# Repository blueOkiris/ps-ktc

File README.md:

# Polymath Studio Keyboard/Trackball Combo

NOTE: Project still in development!!!!

## Description

A keyboard and trackball in one, for efficient computer usage.

Like the [PS-OHK](https://github.com/blueOkiris/ps-ohk/), the PS-KTC attempts to provide an efficiently laid out keyboard which doesn't require moving your hands back and forth from the mouse.

Unlike the PS-OHK, it accomplishes this while allowing for typing quickly via using both hands. This is done by placing a trackball in the middle of the keyboard!

## Layout

Like the PS-OHK, the PS-KTC uses a custom keyboard layout designed around placing commonly used characters right on the home row followed by similar sounds being near each other. It also aims to be roughly a 100% keyboard, although a few shortcuts are taken.

Layout:

```
F1  F2  F3  F4  F5  F6                      F7  F8  F9  F10 F11 F12

                Hm  End                     PgU PgD

            3#                                      8*
        2@                                              9(
            F   4%                              7&  L
        D                                               U
Esc 1!      I   K   5%                      6^  P   R       0)
        T                                               O
Tab C       V   A   Y   LClk           RClk H   E   J       M
        X                                               W
Sft S       [{  G   ,<  Scrl                .>  B   ]}      N   `~
        ;:                Whl                          '"
CLk Z       \|  Ins BSp Del               -----     /?      Q
                                         /Track\
    =+  Up      Ctl Sp  Win             | Ball  |           -_   
                                         \     /    
    Lft Dwn Rt  Alt Ret Cmp               -----     
```

Where the home row is S, T, I, A, Space, Trackball, E, R, O, N

There are 82 keys here. Why not 100? Well, there are few reasons:

1. Due to the every key being available and close to a finger in this arrangement, there is no need for the 10 num-pad digits nor the Num Lock nor the num-pad duplicates of /, \*, -, +, Return, and \./Delete. That's 100 - 10 - 7 = 83
2. No Print Screen, Scroll Lock, or Pause because, let's be real, the vast majority of people, myself included, do not need these keys. Maybe Print Screen, but Super + Shift + S is a great key combo for screenshot, so Print Screen is not needed. That's 83 - 3 = 80 keys
3. Mouse clicks as keys. 82 (middle click = left + right)

## Cost

If you go with the recommended JLCPCB, Tindie, and Amazon links, the cost is roughly broken down like so

| Part                    | Cost (w/ shipping) |
|:-----------------------:|:------------------:|
| PCBs                    | $101.01            |
| Motion Sensor           | $39.98             |
| Rotary Encoder  + Wires | $44.20             |
| Total                   | $185.19            |

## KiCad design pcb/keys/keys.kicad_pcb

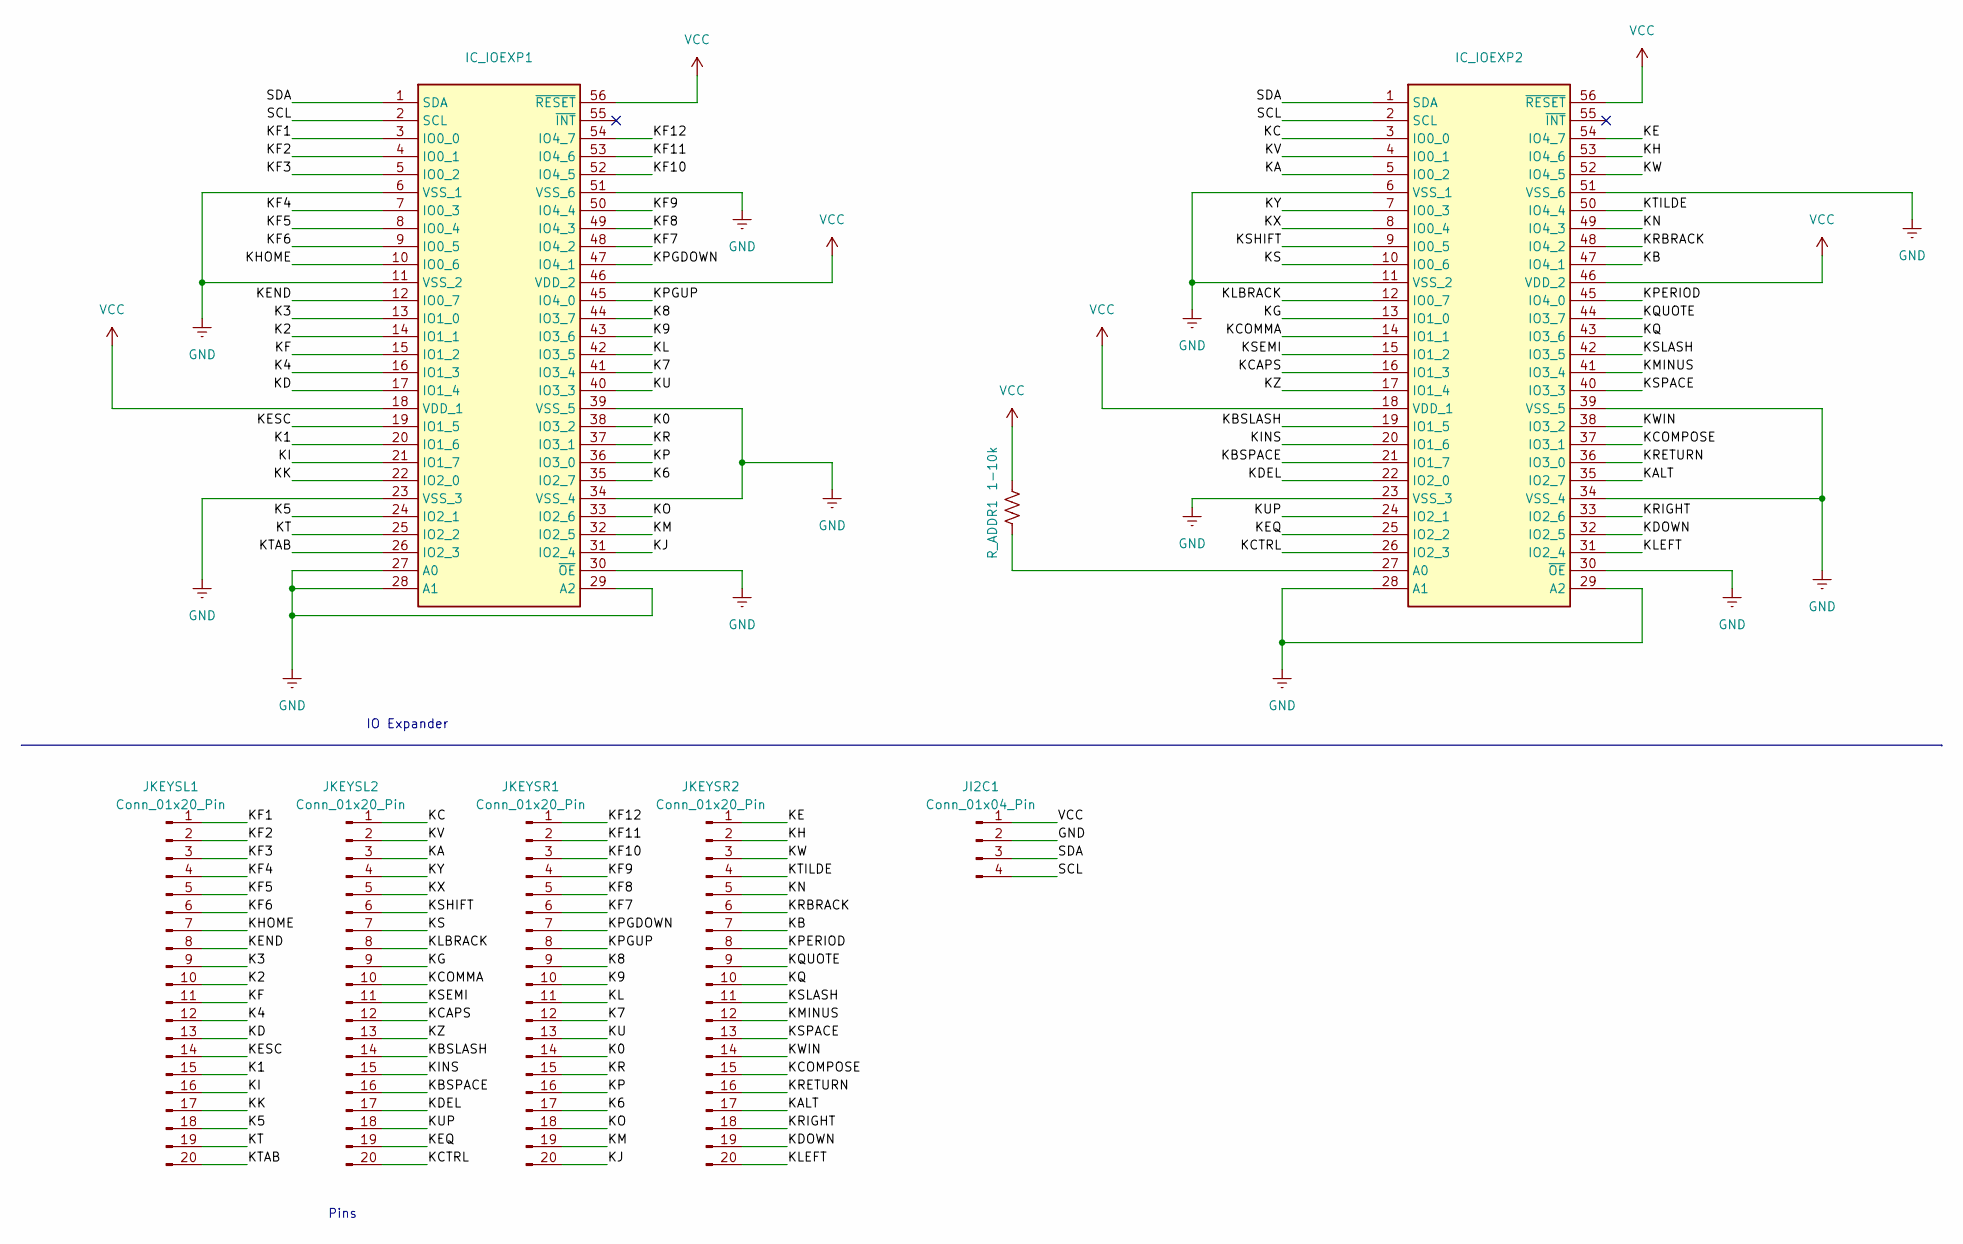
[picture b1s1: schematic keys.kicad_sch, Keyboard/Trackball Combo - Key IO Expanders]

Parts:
IC_IOEXP1, IC_IOEXP2: SOP50P810X120-56N; Mouser Part Number 771-PCA9505DGGY
JI2C1: Conn_01x04_Pin; PinHeader_1x04_P2.54mm_Vertical
JKEYSL1, JKEYSL2: Conn_01x20_Pin; PinHeader_1x20_P2.54mm_Vertical
JKEYSR1, JKEYSR2: Conn_01x20_Pin; PinHeader_1x20_P2.54mm_Vertical
R_ADDR1: 1-10k; R_0603_1608Metric

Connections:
/K0: IC_IOEXP1.38 (IO3_2), JKEYSR1.14
/K1: IC_IOEXP1.20 (IO1_6), JKEYSL1.15
/K2: IC_IOEXP1.14 (IO1_1), JKEYSL1.10
/K3: IC_IOEXP1.13 (IO1_0), JKEYSL1.9
/K4: IC_IOEXP1.16 (IO1_3), JKEYSL1.12
/K5: IC_IOEXP1.24 (IO2_1), JKEYSL1.18
/K6: IC_IOEXP1.35 (IO2_7), JKEYSR1.17
/K7: IC_IOEXP1.41 (IO3_4), JKEYSR1.12
/K8: IC_IOEXP1.44 (IO3_7), JKEYSR1.9
/K9: IC_IOEXP1.43 (IO3_6), JKEYSR1.10
/KA: IC_IOEXP2.5 (IO0_2), JKEYSL2.3
/KALT: IC_IOEXP2.35 (IO2_7), JKEYSR2.17
/KB: IC_IOEXP2.47 (IO4_1), JKEYSR2.7
/KBSLASH: IC_IOEXP2.19 (IO1_5), JKEYSL2.14
/KBSPACE: IC_IOEXP2.21 (IO1_7), JKEYSL2.16
/KC: IC_IOEXP2.3 (IO0_0), JKEYSL2.1
/KCAPS: IC_IOEXP2.16 (IO1_3), JKEYSL2.12
/KCOMMA: IC_IOEXP2.14 (IO1_1), JKEYSL2.10
/KCOMPOSE: IC_IOEXP2.37 (IO3_1), JKEYSR2.15
/KCTRL: IC_IOEXP2.26 (IO2_3), JKEYSL2.20
/KD: IC_IOEXP1.17 (IO1_4), JKEYSL1.13
/KDEL: IC_IOEXP2.22 (IO2_0), JKEYSL2.17
/KDOWN: IC_IOEXP2.32 (IO2_5), JKEYSR2.19
/KE: IC_IOEXP2.54 (IO4_7), JKEYSR2.1
/KEND: IC_IOEXP1.12 (IO0_7), JKEYSL1.8
/KEQ: IC_IOEXP2.25 (IO2_2), JKEYSL2.19
/KESC: IC_IOEXP1.19 (IO1_5), JKEYSL1.14
/KF: IC_IOEXP1.15 (IO1_2), JKEYSL1.11
/KF1: IC_IOEXP1.3 (IO0_0), JKEYSL1.1
/KF2: IC_IOEXP1.4 (IO0_1), JKEYSL1.2
/KF3: IC_IOEXP1.5 (IO0_2), JKEYSL1.3
/KF4: IC_IOEXP1.7 (IO0_3), JKEYSL1.4
/KF5: IC_IOEXP1.8 (IO0_4), JKEYSL1.5
/KF6: IC_IOEXP1.9 (IO0_5), JKEYSL1.6
/KF7: IC_IOEXP1.48 (IO4_2), JKEYSR1.6
/KF8: IC_IOEXP1.49 (IO4_3), JKEYSR1.5
/KF9: IC_IOEXP1.50 (IO4_4), JKEYSR1.4
/KF10: IC_IOEXP1.52 (IO4_5), JKEYSR1.3
/KF11: IC_IOEXP1.53 (IO4_6), JKEYSR1.2
/KF12: IC_IOEXP1.54 (IO4_7), JKEYSR1.1
/KG: IC_IOEXP2.13 (IO1_0), JKEYSL2.9
/KH: IC_IOEXP2.53 (IO4_6), JKEYSR2.2
/KHOME: IC_IOEXP1.10 (IO0_6), JKEYSL1.7
/KI: IC_IOEXP1.21 (IO1_7), JKEYSL1.16
/KINS: IC_IOEXP2.20 (IO1_6), JKEYSL2.15
/KJ: IC_IOEXP1.31 (IO2_4), JKEYSR1.20
/KK: IC_IOEXP1.22 (IO2_0), JKEYSL1.17
/KL: IC_IOEXP1.42 (IO3_5), JKEYSR1.11
/KLBRACK: IC_IOEXP2.12 (IO0_7), JKEYSL2.8
/KLEFT: IC_IOEXP2.31 (IO2_4), JKEYSR2.20
/KM: IC_IOEXP1.32 (IO2_5), JKEYSR1.19
/KMINUS: IC_IOEXP2.41 (IO3_4), JKEYSR2.12
/KN: IC_IOEXP2.49 (IO4_3), JKEYSR2.5
/KO: IC_IOEXP1.33 (IO2_6), JKEYSR1.18
/KP: IC_IOEXP1.36 (IO3_0), JKEYSR1.16
/KPERIOD: IC_IOEXP2.45 (IO4_0), JKEYSR2.8
/KPGDOWN: IC_IOEXP1.47 (IO4_1), JKEYSR1.7
/KPGUP: IC_IOEXP1.45 (IO4_0), JKEYSR1.8
/KQ: IC_IOEXP2.43 (IO3_6), JKEYSR2.10
/KQUOTE: IC_IOEXP2.44 (IO3_7), JKEYSR2.9
/KR: IC_IOEXP1.37 (IO3_1), JKEYSR1.15
/KRBRACK: IC_IOEXP2.48 (IO4_2), JKEYSR2.6
/KRETURN: IC_IOEXP2.36 (IO3_0), JKEYSR2.16
/KRIGHT: IC_IOEXP2.33 (IO2_6), JKEYSR2.18
/KS: IC_IOEXP2.10 (IO0_6), JKEYSL2.7
/KSEMI: IC_IOEXP2.15 (IO1_2), JKEYSL2.11
/KSHIFT: IC_IOEXP2.9 (IO0_5), JKEYSL2.6
/KSLASH: IC_IOEXP2.42 (IO3_5), JKEYSR2.11
/KSPACE: IC_IOEXP2.40 (IO3_3), JKEYSR2.13
/KT: IC_IOEXP1.25 (IO2_2), JKEYSL1.19
/KTAB: IC_IOEXP1.26 (IO2_3), JKEYSL1.20
/KTILDE: IC_IOEXP2.50 (IO4_4), JKEYSR2.4
/KU: IC_IOEXP1.40 (IO3_3), JKEYSR1.13
/KUP: IC_IOEXP2.24 (IO2_1), JKEYSL2.18
/KV: IC_IOEXP2.4 (IO0_1), JKEYSL2.2
/KW: IC_IOEXP2.52 (IO4_5), JKEYSR2.3
/KWIN: IC_IOEXP2.38 (IO3_2), JKEYSR2.14
/KX: IC_IOEXP2.8 (IO0_4), JKEYSL2.5
/KY: IC_IOEXP2.7 (IO0_3), JKEYSL2.4
/KZ: IC_IOEXP2.17 (IO1_4), JKEYSL2.13
/SCL: IC_IOEXP1.2 (SCL), IC_IOEXP2.2 (SCL), JI2C1.4
/SDA: IC_IOEXP1.1 (SDA), IC_IOEXP2.1 (SDA), JI2C1.3
GND: IC_IOEXP1.6 (VSS_1), IC_IOEXP1.11 (VSS_2), IC_IOEXP1.23 (VSS_3), IC_IOEXP1.27 (A0), IC_IOEXP1.28 (A1), IC_IOEXP1.29 (A2), IC_IOEXP1.30 (~OE), IC_IOEXP1.34 (VSS_4), IC_IOEXP1.39 (VSS_5), IC_IOEXP1.51 (VSS_6), IC_IOEXP2.6 (VSS_1), IC_IOEXP2.11 (VSS_2), IC_IOEXP2.23 (VSS_3), IC_IOEXP2.28 (A1), IC_IOEXP2.29 (A2), IC_IOEXP2.30 (~OE), IC_IOEXP2.34 (VSS_4), IC_IOEXP2.39 (VSS_5), IC_IOEXP2.51 (VSS_6), JI2C1.2
VCC: IC_IOEXP1.18 (VDD_1), IC_IOEXP1.46 (VDD_2), IC_IOEXP1.56 (~RESET), IC_IOEXP2.18 (VDD_1), IC_IOEXP2.46 (VDD_2), IC_IOEXP2.56 (~RESET), JI2C1.1, R_ADDR1.1

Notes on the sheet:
IO Expander
Pins

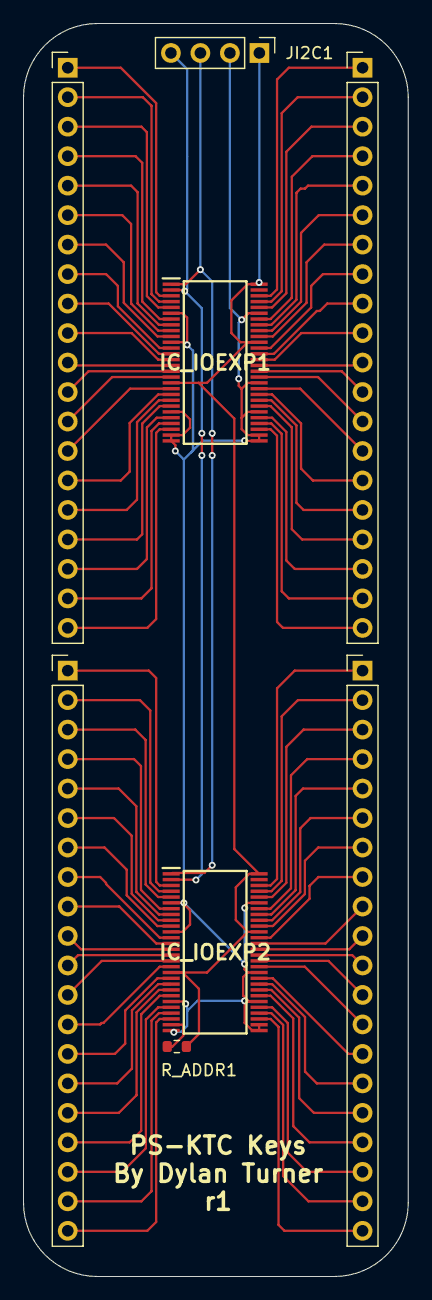
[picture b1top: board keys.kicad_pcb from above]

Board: 2 copper layers, 33.1 x 107.9 mm, 8 parts (0 on the bottom side), 84 nets.

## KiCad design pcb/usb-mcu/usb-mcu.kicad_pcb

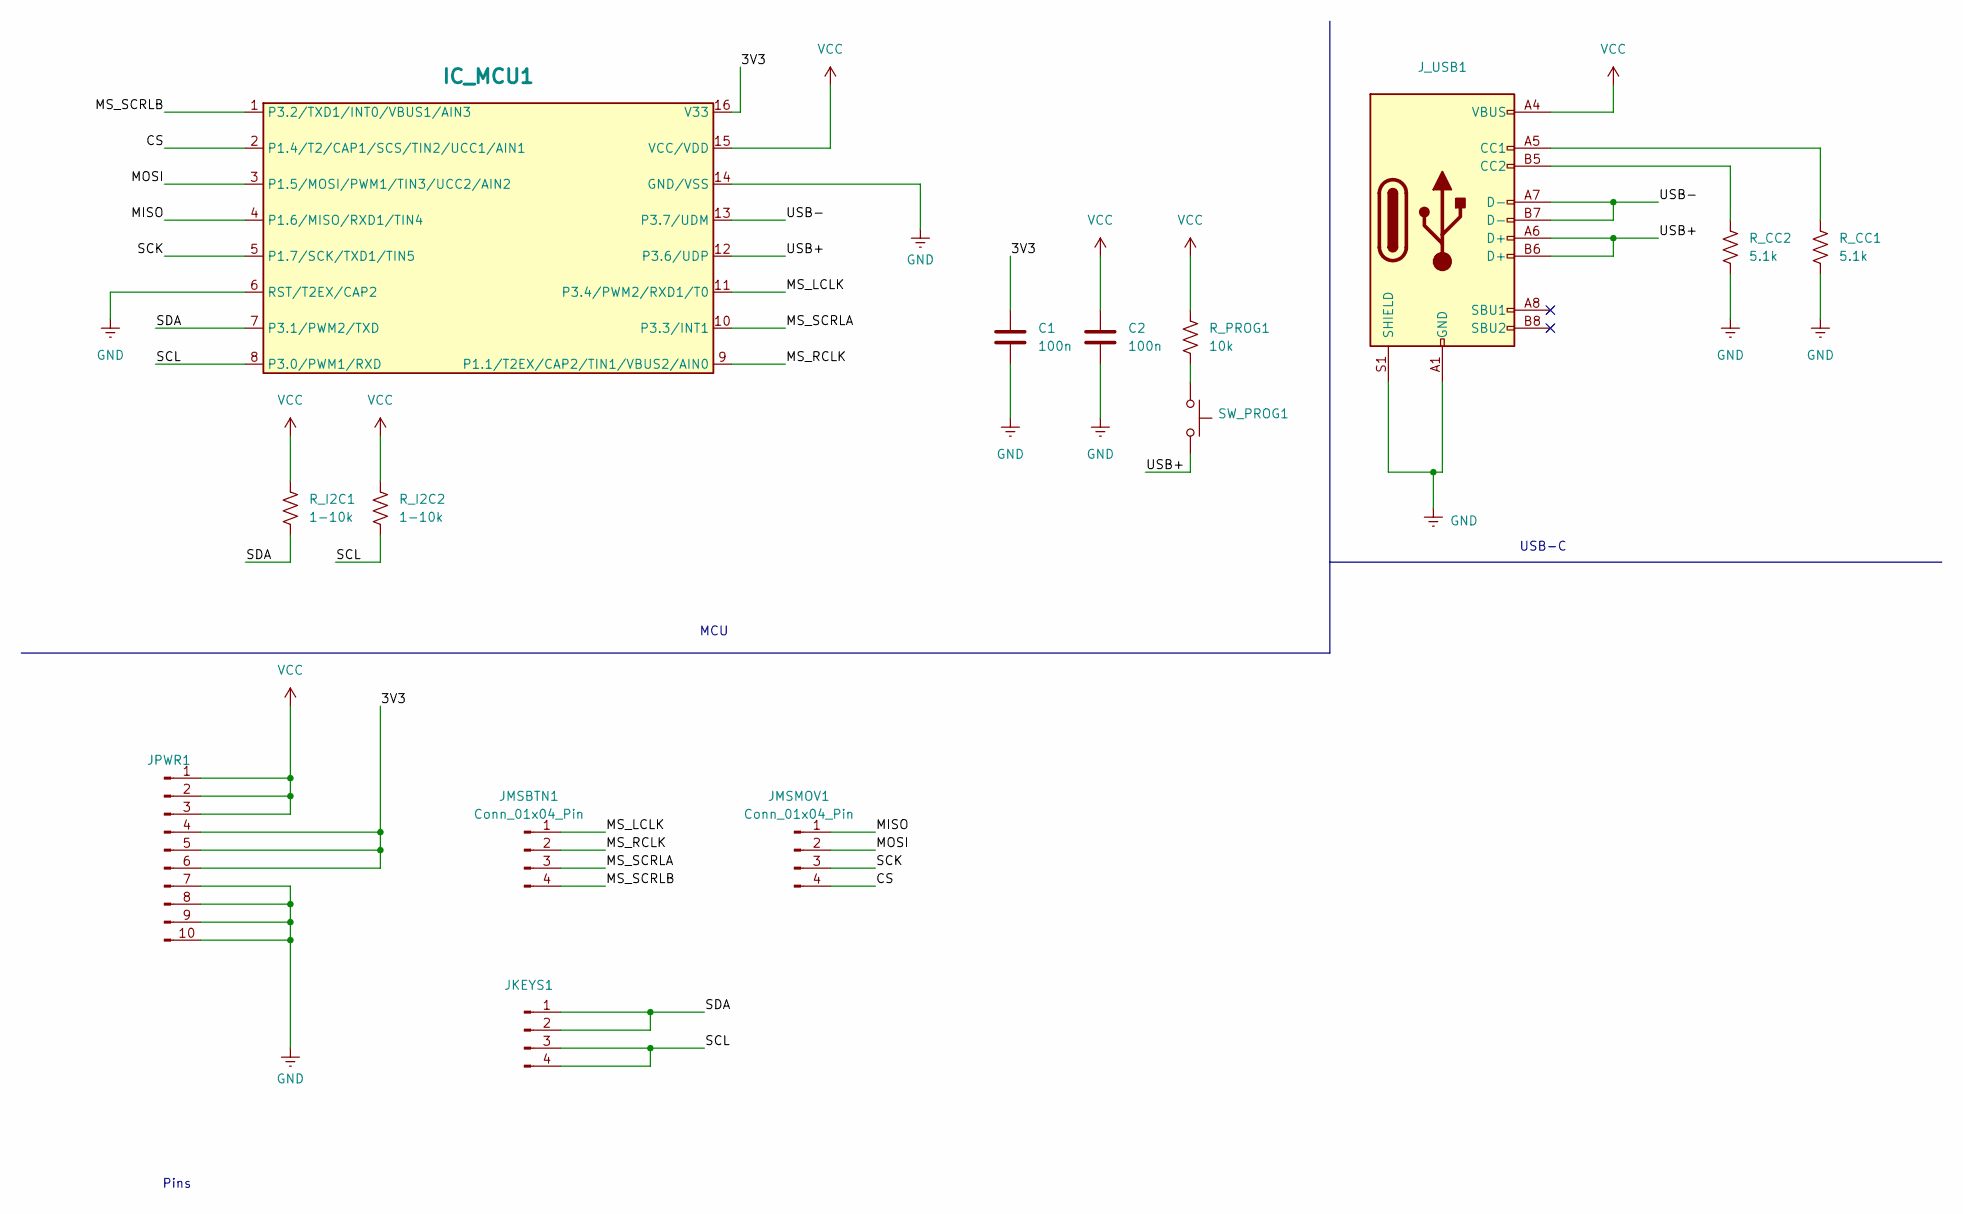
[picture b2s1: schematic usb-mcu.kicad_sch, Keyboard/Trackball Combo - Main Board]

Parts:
C1, C2: 100n; C_0603_1608Metric
IC_MCU1: SOIC-16_3.9x9.9mm_Pitch1.27mm
JKEYS1: PinHeader_1x04_P2.54mm_Vertical
JMSBTN1: Conn_01x04_Pin; PinHeader_1x04_P2.54mm_Vertical
JMSMOV1: Conn_01x04_Pin; PinHeader_1x04_P2.54mm_Vertical
JPWR1: PinHeader_1x10_P2.54mm_Vertical
J_USB1: USB_C_Receptacle_HCTL_HC-TYPE-C-16P-01A
R_CC1, R_CC2: 5.1k; R_0603_1608Metric
R_I2C1, R_I2C2: 1-10k; R_0603_1608Metric
R_PROG1: 10k; R_0603_1608Metric
SW_PROG1: SW_Push_1P1T_NO_6x6mm_H9.5mm

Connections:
/3V3: C1.1, IC_MCU1.16 (V33), JPWR1.4, JPWR1.5, JPWR1.6
/CS: IC_MCU1.2 (P1.4/T2/CAP1/SCS/TIN2/UCC1/AIN1), JMSMOV1.4
/MISO: IC_MCU1.4 (P1.6/MISO/RXD1/TIN4), JMSMOV1.1
/MOSI: IC_MCU1.3 (P1.5/MOSI/PWM1/TIN3/UCC2/AIN2), JMSMOV1.2
/MS_LCLK: IC_MCU1.11 (P3.4/PWM2/RXD1/T0), JMSBTN1.1
/MS_RCLK: IC_MCU1.9 (P1.1/T2EX/CAP2/TIN1/VBUS2/AIN0), JMSBTN1.2
/MS_SCRLA: IC_MCU1.10 (P3.3/INT1), JMSBTN1.3
/MS_SCRLB: IC_MCU1.1 (P3.2/TXD1/INT0/VBUS1/AIN3), JMSBTN1.4
/SCK: IC_MCU1.5 (P1.7/SCK/TXD1/TIN5), JMSMOV1.3
/SCL: IC_MCU1.8 (P3.0/PWM1/RXD), JKEYS1.3, JKEYS1.4, R_I2C2.2
/SDA: IC_MCU1.7 (P3.1/PWM2/TXD), JKEYS1.1, JKEYS1.2, R_I2C1.2
/USB+: IC_MCU1.12 (P3.6/UDP), J_USB1.A6 (D+), J_USB1.B6 (D+), SW_PROG1.2
/USB-: IC_MCU1.13 (P3.7/UDM), J_USB1.A7 (D-), J_USB1.B7 (D-)
GND: C1.2, C2.2, IC_MCU1.6 (RST/T2EX/CAP2), IC_MCU1.14 (GND/VSS), JPWR1.7, JPWR1.8, JPWR1.9, JPWR1.10, J_USB1.A1 (GND), J_USB1.A12 (GND), J_USB1.B1 (GND), J_USB1.B12 (GND), J_USB1.S1 (SHIELD), R_CC1.2, R_CC2.2
unnamed: J_USB1.A5 (CC1), R_CC1.1
unnamed: J_USB1.B5 (CC2), R_CC2.1
unnamed: R_PROG1.2, SW_PROG1.1
VCC: C2.1, IC_MCU1.15 (VCC/VDD), JPWR1.1, JPWR1.2, JPWR1.3, J_USB1.A4 (VBUS), J_USB1.A9 (VBUS), J_USB1.B4 (VBUS), J_USB1.B9 (VBUS), R_I2C1.1, R_I2C2.1, R_PROG1.1

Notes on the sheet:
USB-C
Pins
MCU

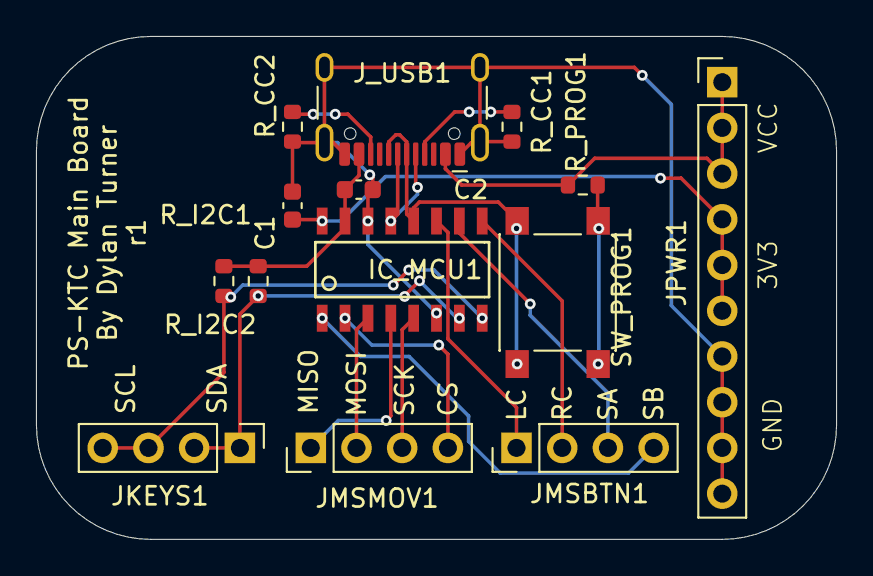
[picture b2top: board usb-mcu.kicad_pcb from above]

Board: 2 copper layers, 44.5 x 27.9 mm, 14 parts (0 on the bottom side), 18 nets.

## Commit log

2024-10-01 Project start
2024-10-01 README: add cost estimation
2024-10-01 README: add note about development
